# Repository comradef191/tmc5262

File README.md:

# TMC5262
This repository contains KiCAD 10.0 files for two stepper-motor driver boards based on the Trinamic [TMC5262](https://www.analog.com/en/products/tmc5262.html) driver.

**Notice:** As of May 9th 2026, these boards have not yet been tested. The initial release of these boards contains the text 'PROTOTYPE' on the silkscreen to reflect this.

You will have errors on opening the files if you do not have the [nasin-nanpa font](https://github.com/ETBCOR/nasin-nanpa) installed, used by me for both marking my name and occasionally eastereggs.

These files contain LCSC P/Ns for the SMD components and, on the external board the two large capacitors. Specific P/Ns are not provided for other through-hole components.

While these files are intended to be compatible with JLCPCB assembly, as of May 9th 2026 only Digikey is [selling the driver IC](https://www.digikey.com/en/products/detail/analog-devices-inc-maxim-integrated/TMC5262AFV/29292344), thus you will have to solder this component yourself or consign the chips to JLCPCB.

## External Driver:

This is a larger board intended for fully-testing the driver and all its features.

The files for this board are located in the *'Motor-TMC5262-external'* directory.

- **Dimensions:** 50x50mm PCB, with 43x3mm M3 mounting holes.
-**Voltage Input:** 65v max, 1x2 5.08mm-Pitch screwterminal
- **Coil Output:** 4A max, 1x4 5.08mm-Pitch screwterminal
- **DIAG0 & DIAG1:** DIAG0 is on the 'STANDALONE IO' connector, DIAG1 is on the 'COMMS IO' connector. Connecting of both or either is not required.
- **Encoder:** ENCN, ENCA, ENCB pins broken-out to 2x3 header
- **Brake Resistor:** None built-in, use header to connect externally
- **Connectivity:** Connects to the MCU using two 6-pin JST-XH connectors

## Stepstick Driver:

This is a small board intended for testing compatibility with existing stepstick-based mainboards, due to its smaller size caution to ensure no overheating should be taken.

The files for this board are located in the *'Motor-TMC5262-stepstick'* directory.

- **Dimensions:** 15.74x20.82mm StepStick
- **Voltage Input:** 65v max (Do not exceed rating of your mainboard)
- **Coil Output:** 3A max, B1/B2/A2/A1 instead of B2/A2/A1/B1
- **DIAG0 & DIAG1:** DIAG0 & DIAG1 connected per other StepSticks with two DIAG pins (e.g. [TMC22x SilentStepStick](https://learn.watterott.com/silentstepstick/pinconfig/))
- *Encoder:** Not-Present
- **Brake Resistor:** Not-Present
- **Connectivity:** Connects to the MCU using a standard 'StepStick' style socket. Make sure to set the jumpers to use SPI.

# License
This project is licensed under the CERN OHL V2 - S, see LICENSE.TXT for further information.

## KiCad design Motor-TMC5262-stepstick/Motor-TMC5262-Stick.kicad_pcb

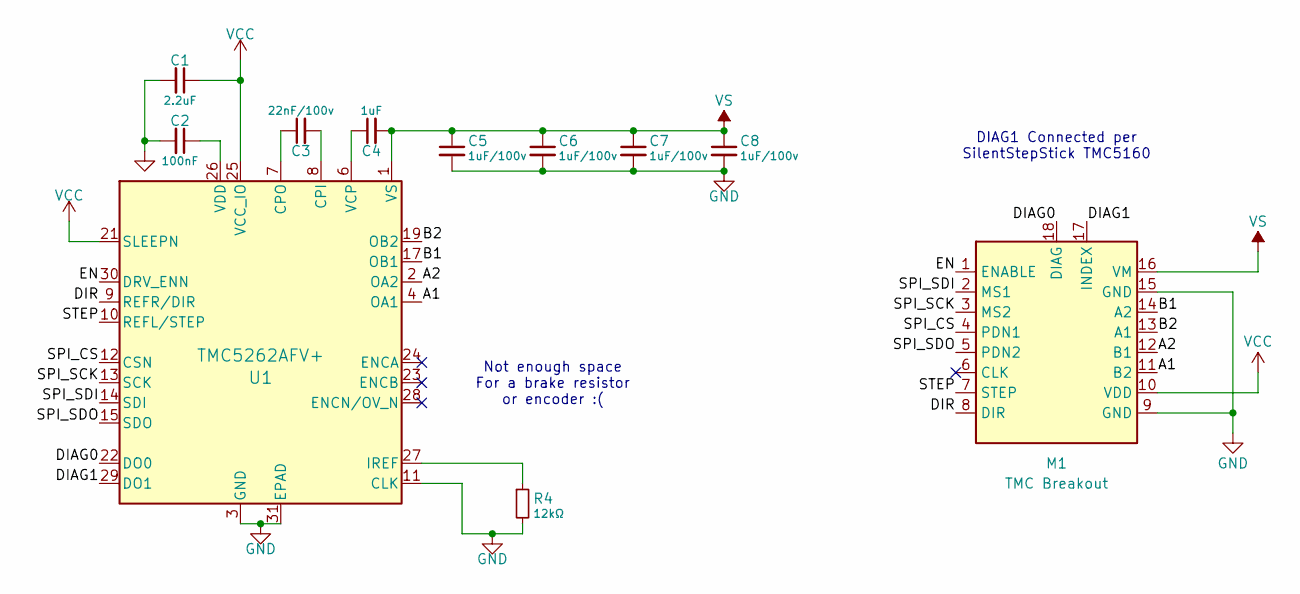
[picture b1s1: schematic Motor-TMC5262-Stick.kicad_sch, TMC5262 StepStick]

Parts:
C1: 2.2uF; C_0402_1005Metric; LCSC C12530
C2: 100nF; C_0402_1005Metric; LCSC C1525
C3: 22nF/100v; C_0603_1608Metric; LCSC C161234
C4: 1uF; C_0402_1005Metric; LCSC C52923
C5, C6, C7, C8: 1uF/100v; C_0805_2012Metric; LCSC C6119928
M1: TMC Breakout; TMC2209 Footprint (Plug)
R4: 12kΩ; R_0402_1005Metric; LCSC C25752
U1: TMC5262AFV+; 30L FC2QFN 6x6 (TMC5262); LCSC C9900140256

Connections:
/A1: M1.11 (B2), U1.4 (OA1)
/A2: M1.12 (B1), U1.2 (OA2)
/B1: M1.14 (A2), U1.17 (OB1)
/B2: M1.13 (A1), U1.19 (OB2)
/DIAG0: M1.18 (DIAG), U1.22 (DO0)
/DIAG1: M1.17 (INDEX), U1.29 (DO1)
/DIR: M1.8 (DIR), U1.9 (REFR/DIR)
/EN: M1.1 (ENABLE), U1.30 (DRV_ENN)
/SPI_CS: M1.4 (PDN1), U1.12 (CSN)
/SPI_SCK: M1.3 (MS2), U1.13 (SCK)
/SPI_SDI: M1.2 (MS1), U1.14 (SDI)
/SPI_SDO: M1.5 (PDN2), U1.15 (SDO)
/STEP: M1.7 (STEP), U1.10 (REFL/STEP)
GND: C1.2, C2.2, C5.2, C6.2, C7.2, C8.2, M1.9 (GND), M1.15 (GND), R4.2, U1.3 (GND), U1.11 (CLK), U1.18 (GND), U1.31 (EPAD)
unnamed: C3.2, U1.8 (CPI)
unnamed: C3.1, U1.7 (CPO)
unnamed: R4.1, U1.27 (IREF)
unnamed: C4.1, U1.6 (VCP)
unnamed: C2.1, U1.26 (VDD)
VCC: C1.1, M1.10 (VDD), U1.21 (SLEEPN), U1.25 (VCC_IO)
VS: C4.2, C5.1, C6.1, C7.1, C8.1, M1.16 (VM), U1.1 (VS), U1.5 (VS), U1.16 (VS), U1.20 (VS)

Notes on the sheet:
Not enough space For a brake resistor or encoder :(
DIAG1 Connected per SilentStepStick TMC5160

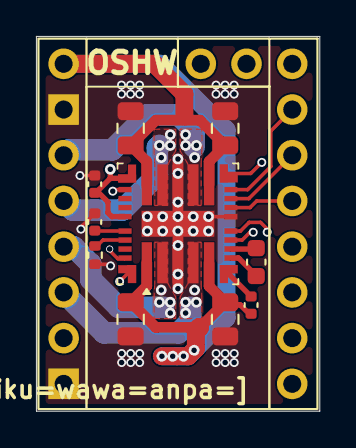
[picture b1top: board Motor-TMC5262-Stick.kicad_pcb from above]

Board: 4 copper layers, 15.7 x 20.8 mm, 11 parts (1 on the bottom side), 21 nets.

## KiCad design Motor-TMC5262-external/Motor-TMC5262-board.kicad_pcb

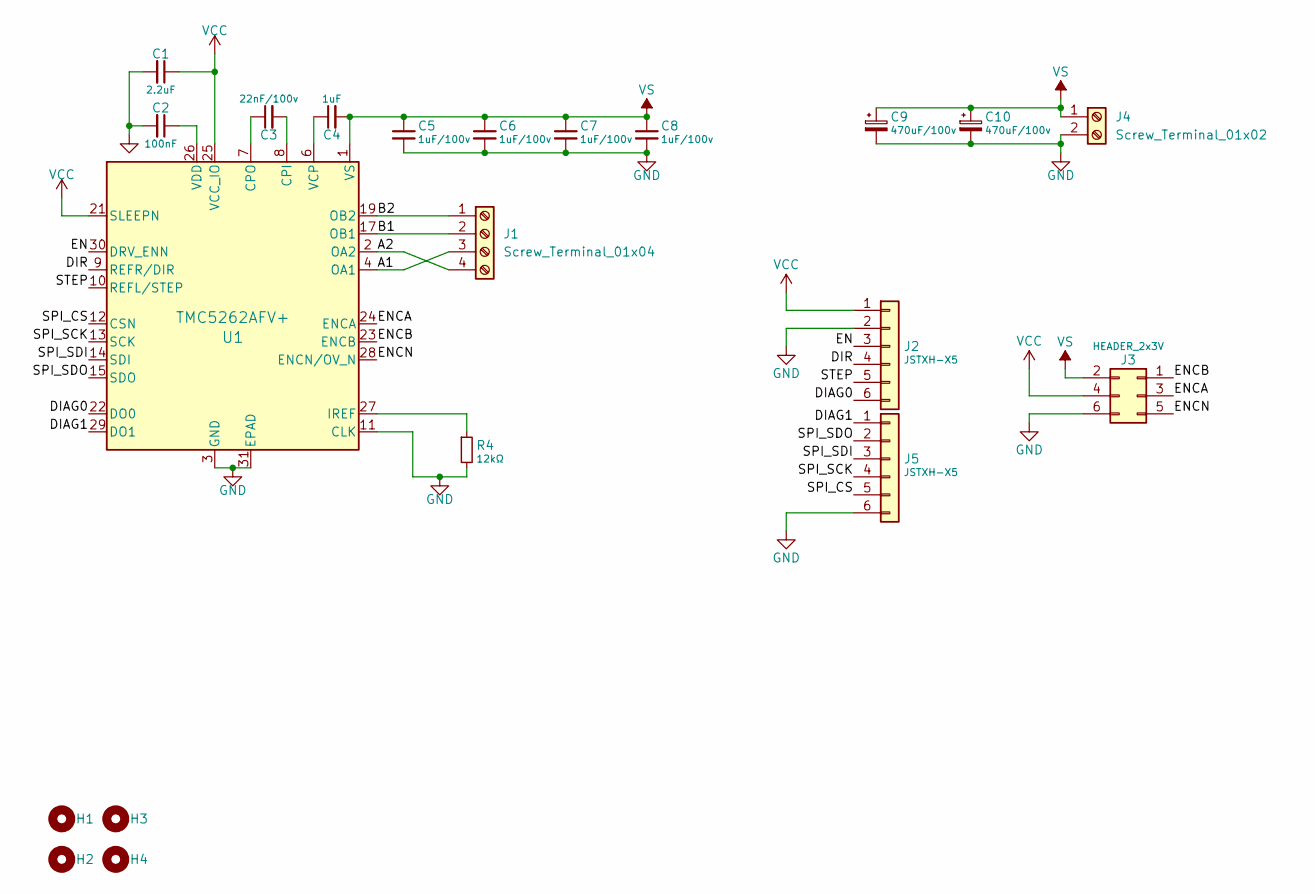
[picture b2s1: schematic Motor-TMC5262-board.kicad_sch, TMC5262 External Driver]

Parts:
C1: 2.2uF; C_0402_1005Metric; LCSC C12530
C2: 100nF; C_0402_1005Metric; LCSC C1525
C3: 22nF/100v; C_0603_1608Metric; LCSC C161234
C4: 1uF; C_0402_1005Metric; LCSC C52923
C5, C6, C7, C8: 1uF/100v; C_0805_2012Metric; LCSC C6119928
C9, C10: 470uF/100v; CP_Radial_D16.0mm_P7.50mm; LCSC C2913975
H1, H2, H3, H4: MountingHole; M3 Mounting Hole ~ Classic - No Keepout
J1: Screw_Terminal_01x04; TerminalBlock_Phoenix_MKDS-3-4-5.08_1x04_P5.08mm_Horizontal
J2, J5: JSTXH-X5; JST_XH_B6B-XH-A_1x06_P2.50mm_Vertical
J3: HEADER_2x3V; PinHeader_2x03_P2.54mm_Vertical
J4: Screw_Terminal_01x02; TerminalBlock_Phoenix_MKDS-1,5-2-5.08_1x02_P5.08mm_Horizont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
R4: 12kΩ; R_0402_1005Metric; LCSC C25752
U1: TMC5262AFV+; 30L FC2QFN 6x6 (TMC5262); LCSC C9900140256

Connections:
/A1: J1.3, U1.4 (OA1)
/A2: J1.4, U1.2 (OA2)
/B1: J1.2, U1.17 (OB1)
/B2: J1.1, U1.19 (OB2)
/DIAG0: J2.6, U1.22 (DO0)
/DIAG1: J5.1, U1.29 (DO1)
/DIR: J2.4, U1.9 (REFR/DIR)
/EN: J2.3, U1.30 (DRV_ENN)
/ENCA: J3.3, U1.24 (ENCA)
/ENCB: J3.1, U1.23 (ENCB)
/ENCN: J3.5, U1.28 (ENCN/OV_N)
/SPI_CS: J5.5, U1.12 (CSN)
/SPI_SCK: J5.4, U1.13 (SCK)
/SPI_SDI: J5.3, U1.14 (SDI)
/SPI_SDO: J5.2, U1.15 (SDO)
/STEP: J2.5, U1.10 (REFL/STEP)
GND: C1.2, C2.2, C5.2, C6.2, C7.2, C8.2, C9.2, C10.2, J2.2, J3.6, J4.2, J5.6, R4.2, U1.3 (GND), U1.11 (CLK), U1.18 (GND), U1.31 (EPAD)
unnamed: C3.2, U1.8 (CPI)
unnamed: C3.1, U1.7 (CPO)
unnamed: R4.1, U1.27 (IREF)
unnamed: C4.1, U1.6 (VCP)
unnamed: C2.1, U1.26 (VDD)
VCC: C1.1, J2.1, J3.4, U1.21 (SLEEPN), U1.25 (VCC_IO)
VS: C4.2, C5.1, C6.1, C7.1, C8.1, C9.1, C10.1, J3.2, J4.1, U1.1 (VS), U1.5 (VS), U1.16 (VS), U1.20 (VS)

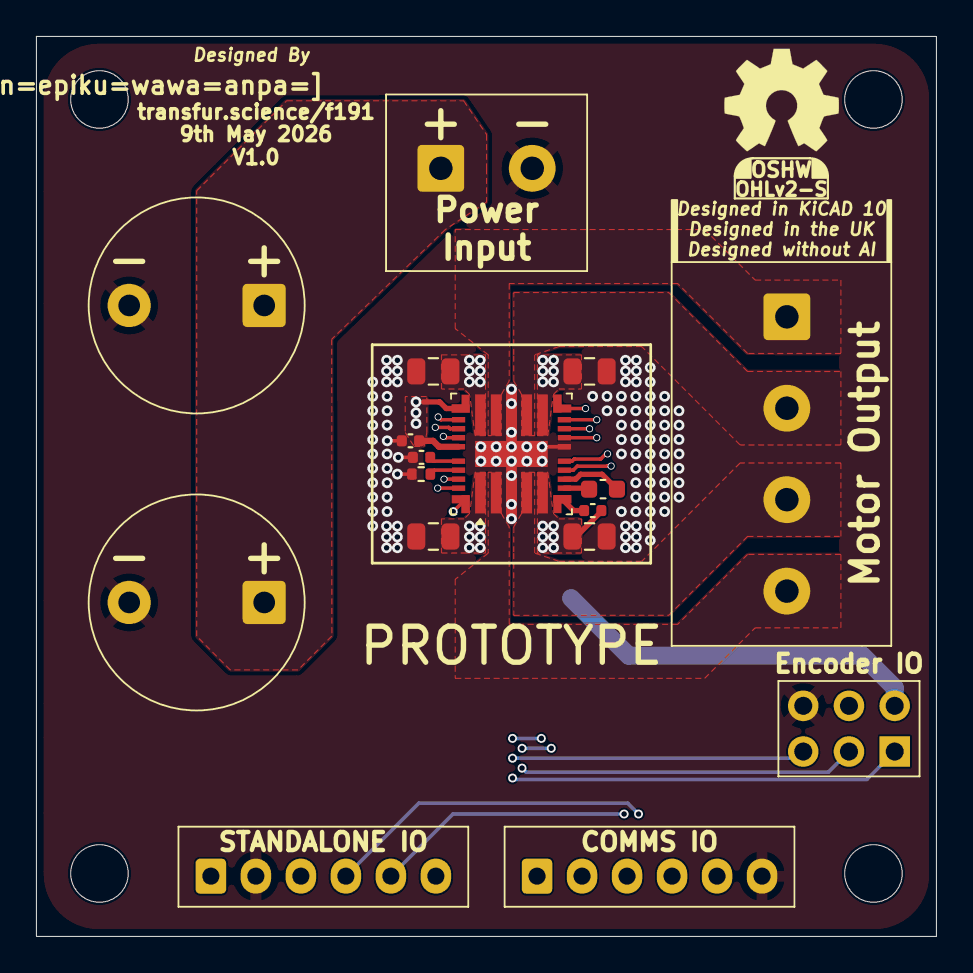
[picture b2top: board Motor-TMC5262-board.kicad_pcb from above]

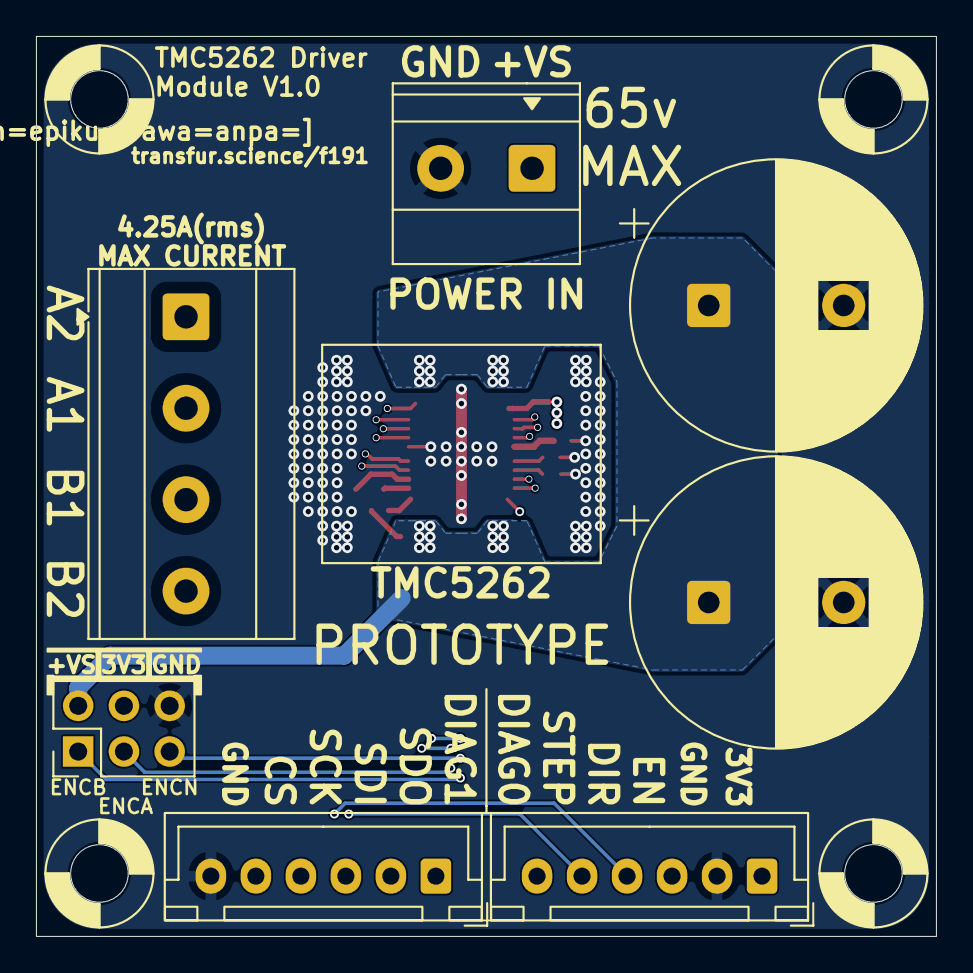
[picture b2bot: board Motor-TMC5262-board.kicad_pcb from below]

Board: 4 copper layers, 50.0 x 50.0 mm, 21 parts (11 on the bottom side), 24 nets.

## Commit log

2026-05-09 Add all project files
2026-05-09 Update README.md
    Fix broken formatting & an incorrect connectivity method for the StepStick.
